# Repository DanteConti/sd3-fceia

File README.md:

# sd3-fceia
Proyecto para sensado de material particulado en aire y sonometro IoT

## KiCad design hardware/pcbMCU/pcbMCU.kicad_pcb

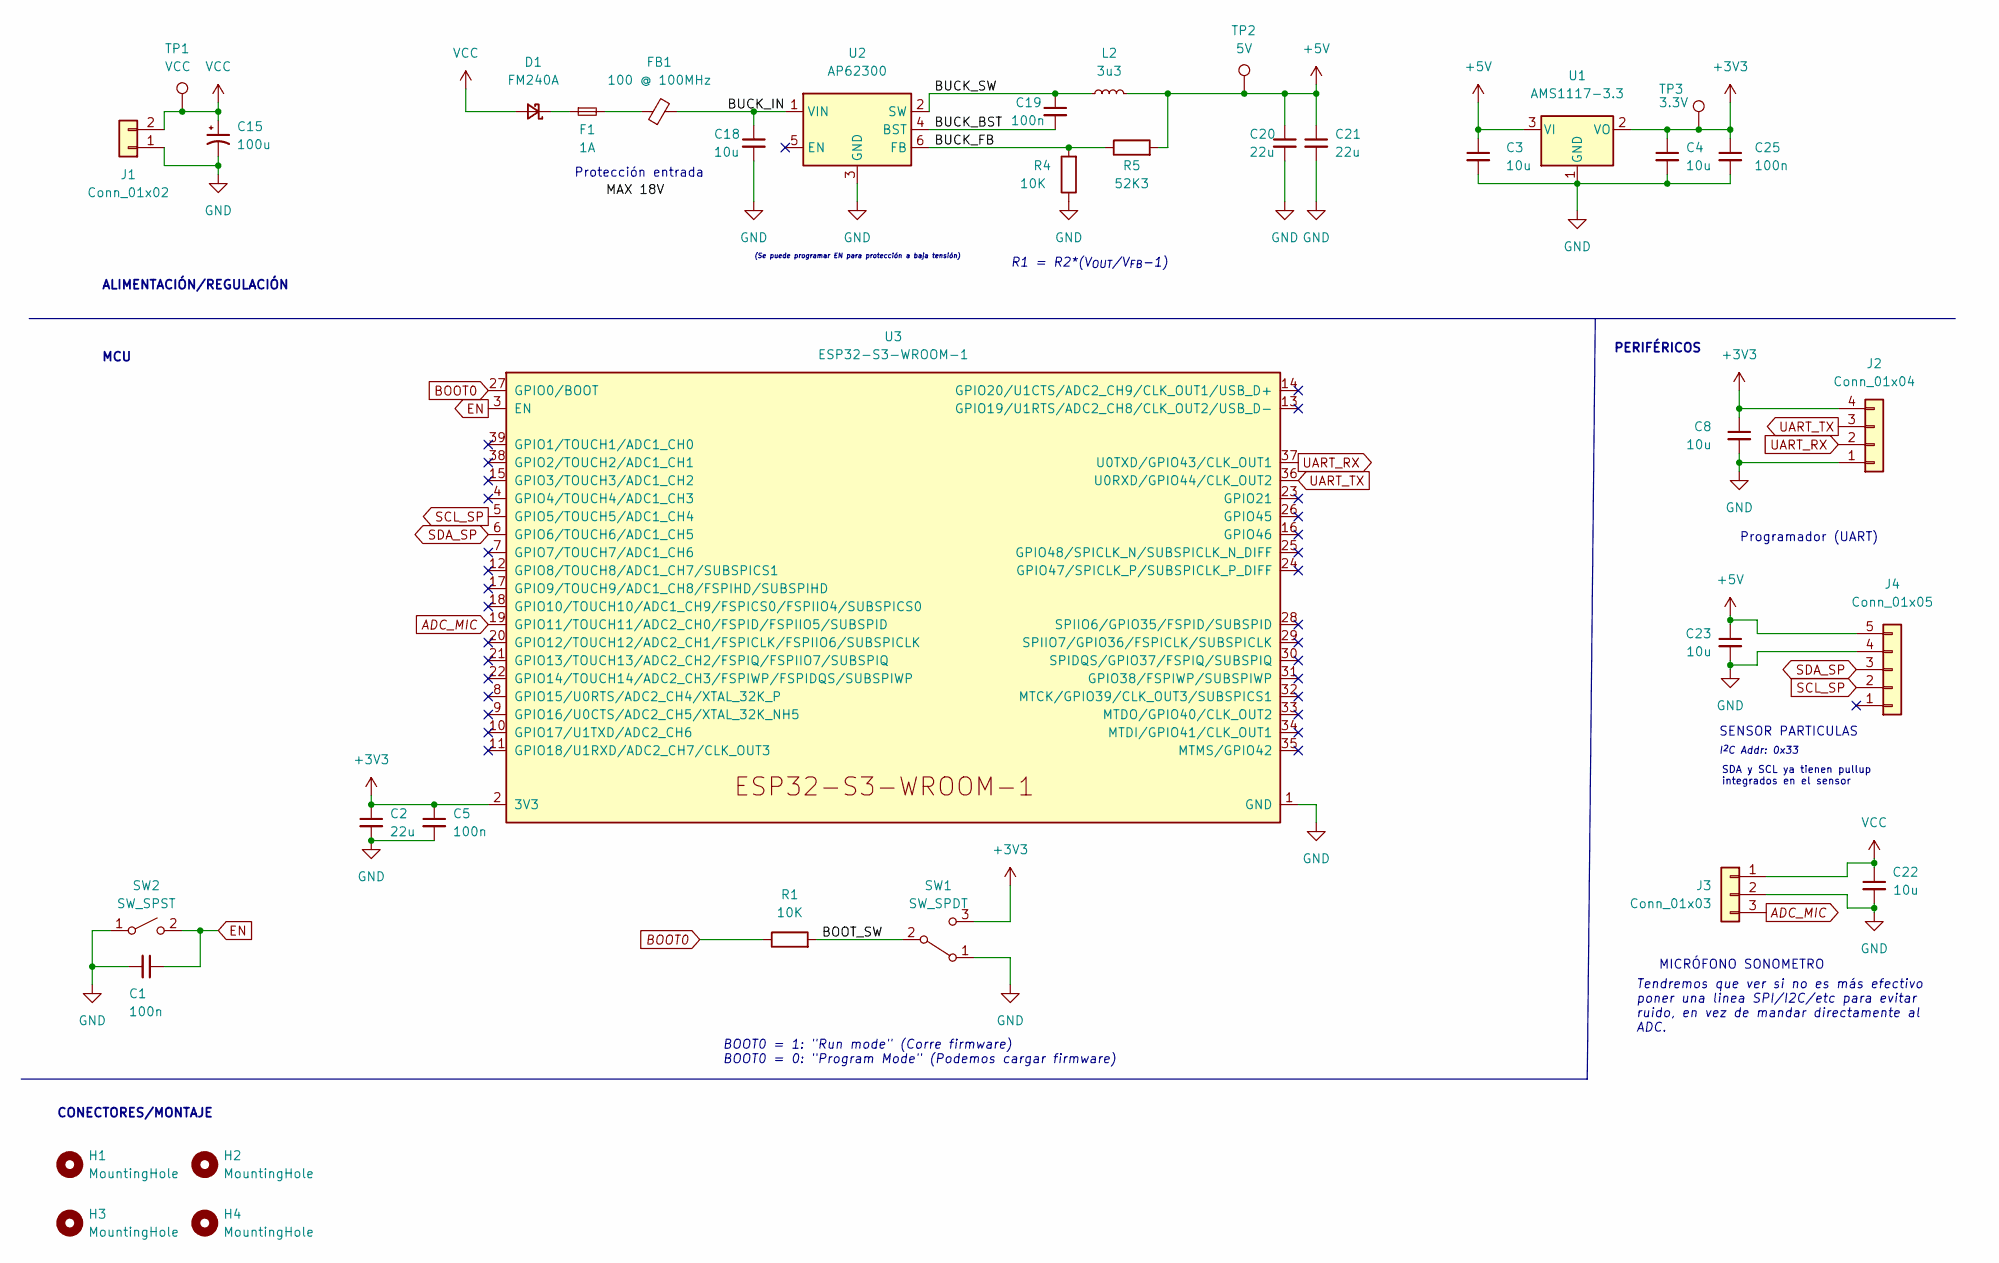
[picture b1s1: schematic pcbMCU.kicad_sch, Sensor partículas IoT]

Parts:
C1, C5, C19, C25: 100n; C_0603_1608Metric_Pad1.08x0.95mm_HandSolder
C2: 22u; C_0603_1608Metric_Pad1.08x0.95mm_HandSolder
C3, C4, C8, C18, C22, C23: 10u; C_0805_2012Metric_Pad1.18x1.45mm_HandSolder
C15: 100u; CP_Radial_D8.0mm_P5.00mm
C20, C21: 22u; C_0805_2012Metric_Pad1.18x1.45mm_HandSolder
D1: FM240A; D_SMB
F1: 1A; Fuse_1206_3216Metric_Pad1.42x1.75mm_HandSolder
FB1: 100 @ 100MHz; L_0603_1608Metric_Pad1.05x0.95mm_HandSolder
H1, H2, H3, H4: MountingHole; MountingHole_5mm_Pad_Via
J1: Conn_01x02; PinSocket_1x02_P2.54mm_Vertical
J2: Conn_01x04; PinHeader_1x04_P2.54mm_Vertical
J3: Conn_01x03; JST_GH_SM03B-GHS-TB_1x03-1MP_P1.25mm_Horizontal
J4: Conn_01x05; JST_GH_SM05B-GHS-TB_1x05-1MP_P1.25mm_Horizontal
L2: 3u3; L_0805_2012Metric_Pad1.15x1.40mm_HandSolder
R1, R4: 10K; R_0603_1608Metric_Pad0.98x0.95mm_HandSolder
R5: 52K3; R_0603_1608Metric_Pad0.98x0.95mm_HandSolder
SW1: SW_SPDT; PinHeader_1x03_P2.54mm_Vertical
SW2: SW_SPST; KSA_Tactile_SPST
TP1: VCC; TestPoint_Pad_D2.0mm
TP2: 5V; TestPoint_Pad_D2.0mm
TP3: 3.3V; TestPoint_Pad_D2.0mm
U1: AMS1117-3.3; SOT-223-3_TabPin2
U2: AP62300; SOT-563
U3: ESP32-S3-WROOM-1; ESP32-S3-WROOM-1U

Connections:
+3V3: C2.1, C4.1, C5.1, C8.1, C25.1, J2.4, SW1.3 (C), TP3.1, U1.2 (VO), U3.2 (3V3)
+5V: C3.1, C20.1, C21.1, C23.1, J4.5, L2.2, R5.2, TP2.1, U1.3 (VI)
/BOOT_SW: R1.2, SW1.2 (B)
/BUCK_BST: C19.2, U2.4 (BST)
/BUCK_FB: R4.2, R5.1, U2.6 (FB)
/BUCK_IN: C18.1, FB1.2, U2.1 (VIN)
/BUCK_SW: C19.1, L2.1, U2.2 (SW)
ADC_MIC: J3.3, U3.19 (GPIO11/TOUCH11/ADC2_CH0/FSPID/FSPIIO5/S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)
BOOT0: R1.1, U3.27 (GPIO0/BOOT)
EN: C1.1, SW2.2 (B), U3.3 (EN)
GND: C1.2, C2.2, C3.2, C4.2, C5.2, C8.2, C15.2, C18.2, C20.2, C21.2, C22.2, C23.2, C25.2, J1.1, J2.1, J3.2, J4.4, R4.1, SW1.1 (A), SW2.1 (A), U1.1 (GND), U2.3 (GND), U3.1 (GND), U3.40 (GND), U3.41 (GND)
unnamed: D1.1 (K), F1.1
unnamed: F1.2, FB1.1
SCL_SP: J4.2, U3.5 (GPIO5/TOUCH5/ADC1_CH4)
SDA_SP: J4.3, U3.6 (GPIO6/TOUCH6/ADC1_CH5)
UART_RX: J2.2, U3.37 (U0TXD/GPIO43/CLK_OUT1)
UART_TX: J2.3, U3.36 (U0RXD/GPIO44/CLK_OUT2)
VCC: C15.1, C22.1, D1.2 (A), J1.2, J3.1, TP1.1

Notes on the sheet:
SDA y SCL ya tienen pullup integrados en el sensor
ALIMENTACIÓN/REGULACIÓN
Protección entrada
(Se puede programar EN para protección a baja tensión)
MCU
MICRÓFONO SONOMETRO
BOOT0 = 1: "Run mode" (Corre firmware) BOOT0 = 0: "Program Mode" (Podemos cargar firmware)
I^{2}C Addr: 0x33
SENSOR PARTICULAS
Programador (UART)
CONECTORES/MONTAJE
PERIFÉRICOS
R1 = R2*(V_{OUT}/V_{FB}-1)
Tendremos que ver si no es más efectivo poner una linea SPI/I2C/etc para evitar ruido, en vez de mandar directamente al ADC.

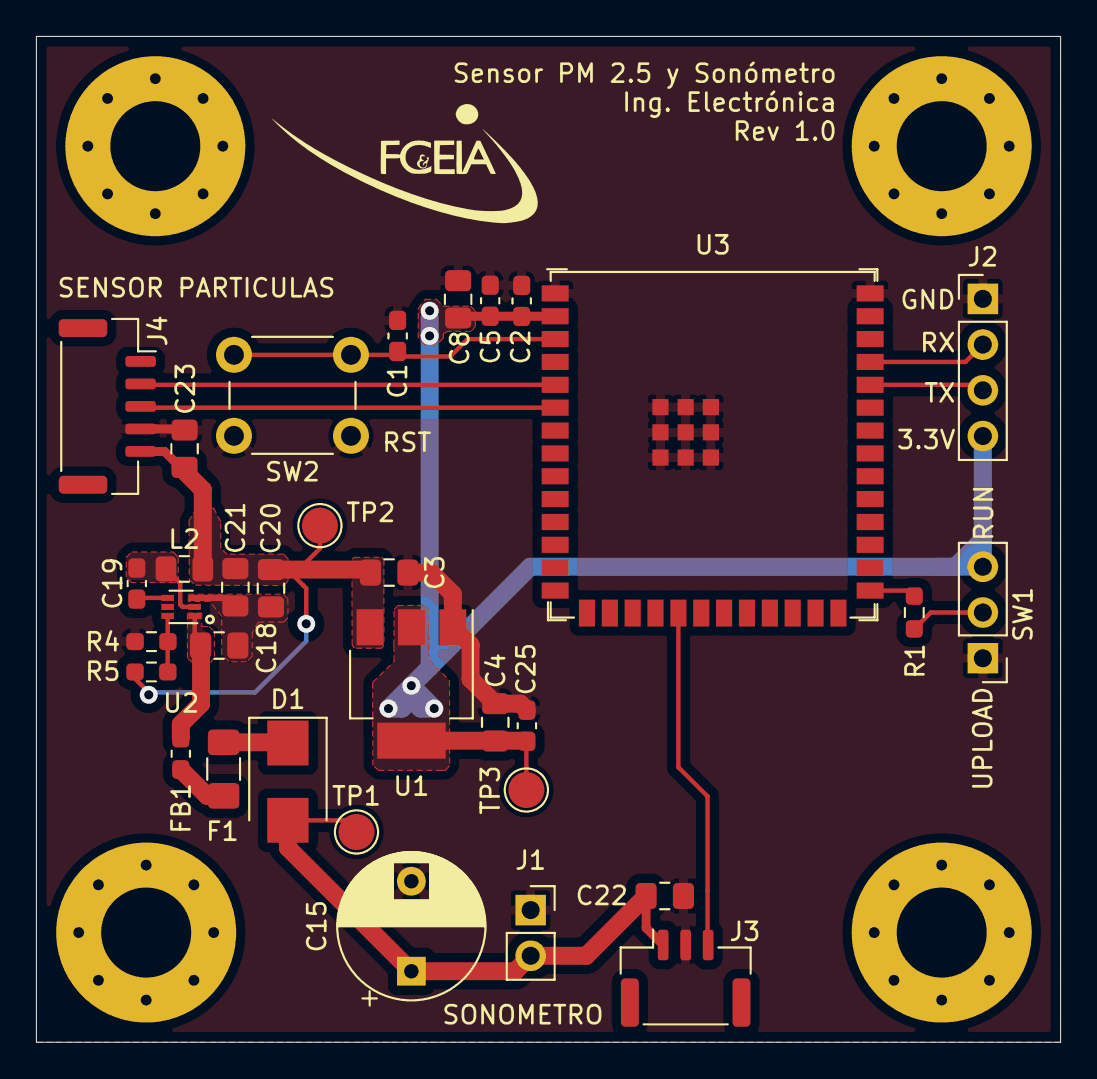
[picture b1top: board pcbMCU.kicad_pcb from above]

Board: 2 copper layers, 56.9 x 55.9 mm, 37 parts (0 on the bottom side), 18 nets.

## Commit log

2022-10-27 commit inicial kicad
2022-10-27 Simbolo inicial STM32
2022-10-28 Rollback a STM32F103
2022-10-28 Regulación de alimentación de entrada
2022-10-30 Rev1 terminada
2022-10-30 Añadido medidor partículas
2022-10-30 Cambio de MCU a STM32L4 + Firmware Inicial
2022-10-30 Agregado librería LoRa
2022-11-08 Añadido convertidor buck para batería
2022-11-12 Cambio conector SP. Añadido módulo LoRa 915Mhz
2022-11-12 Footprint inicial de los componentes
2022-11-13 Footprint modulo RA-02 THT creado. Pasados componentes a PCB
2022-11-24 Cambio a ESP32
2022-11-30 Esquema de PCB inicial, agrupación general de componentes
2022-12-01 PCB lista para primera revisión
2022-12-01 Añadido modelos 3D + Gráficos/descripciones
